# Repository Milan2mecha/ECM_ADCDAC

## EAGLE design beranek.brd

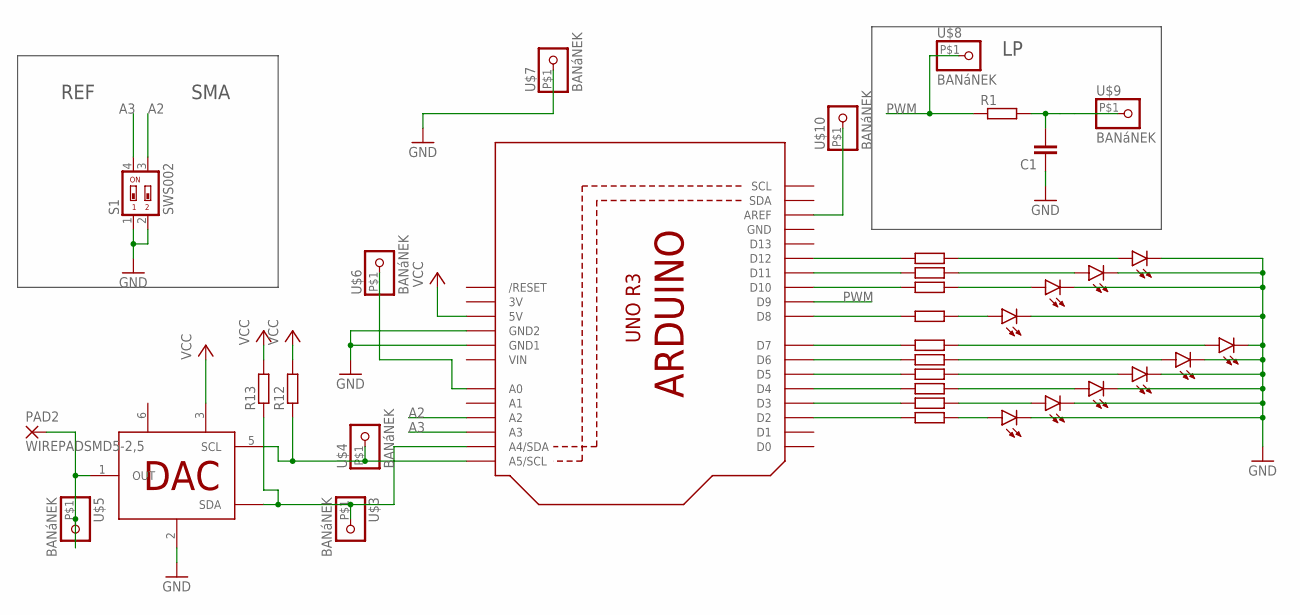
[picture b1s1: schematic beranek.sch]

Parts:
C1: C-EUC0805; C0805
LD2, LD3, LD4, LD5, LD6, LD7, LD8, LD9, LD10, LD11: PL006-WCR12; SOT23
PAD2: WIREPADSMD5-2,5; 5-2,5
Q1: ARDUINOR3-NOIOREF-NOTEXT; ARDUINOR3-NOTEXT-NOIOREF
R1, R2, R3, R4, R5, R6, R7, R8, R9, R10, R11: R-EU_R1206; R1206
R12, R13: R-EU_R0805; R0805
S1: SWS002; SMS-002
U$1: MCP4726; TSOT23-6
U$3, U$4, U$5, U$6, U$7, U$8, U$9, U$10: BANáNEK; BANANEK

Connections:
3V: Q1.3V
A2: Q1.A2, S1.3
A3: Q1.A3, S1.4
GND: C1.1, LD2.3 (C), LD3.3 (C), LD4.3 (C), LD5.3 (C), LD6.3 (C), LD7.3 (C), LD8.3 (C), LD9.3 (C), LD10.3 (C), LD11.3 (C), Q1.GND, Q1.GND1, Q1.GND2, S1.1, S1.2, U$1.2 (VSS), U$7.P$1
unnamed: PAD2.1, U$1.1 (OUT), U$5.P$1
unnamed: Q1.A4 (A4/SDA), R13.1, U$1.4 (SDA), U$3.P$1
unnamed: Q1.A0, U$6.P$1
unnamed: C1.2, R1.2, U$9.P$1
unnamed: Q1.D2, R2.2
unnamed: Q1.D3, R3.2
unnamed: Q1.D4, R4.2
unnamed: Q1.D5, R5.2
unnamed: Q1.D6, R6.2
unnamed: Q1.D7, R7.2
unnamed: Q1.D8, R8.2
unnamed: LD2.1 (A), R2.1
unnamed: LD3.1 (A), R3.1
unnamed: LD4.1 (A), R4.1
unnamed: LD7.1 (A), R7.1
unnamed: LD6.1 (A), R6.1
unnamed: LD5.1 (A), R5.1
unnamed: LD8.1 (A), R8.1
unnamed: Q1.D10, R9.2
unnamed: LD9.1 (A), R9.1
unnamed: Q1.D11, R10.2
unnamed: LD10.1 (A), R10.1
unnamed: Q1.D12, R11.2
unnamed: LD11.1 (A), R11.1
unnamed: Q1.AREF, U$10.P$1
PWM: Q1.D9, R1.1, U$8.P$1
SCL: Q1.A5 (A5/SCL), R12.1, U$1.5 (SCL), U$4.P$1
VCC: Q1.5V, R12.2, R13.2, U$1.3 (VDD)
VIN: Q1.VIN

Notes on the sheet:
REF
SMA

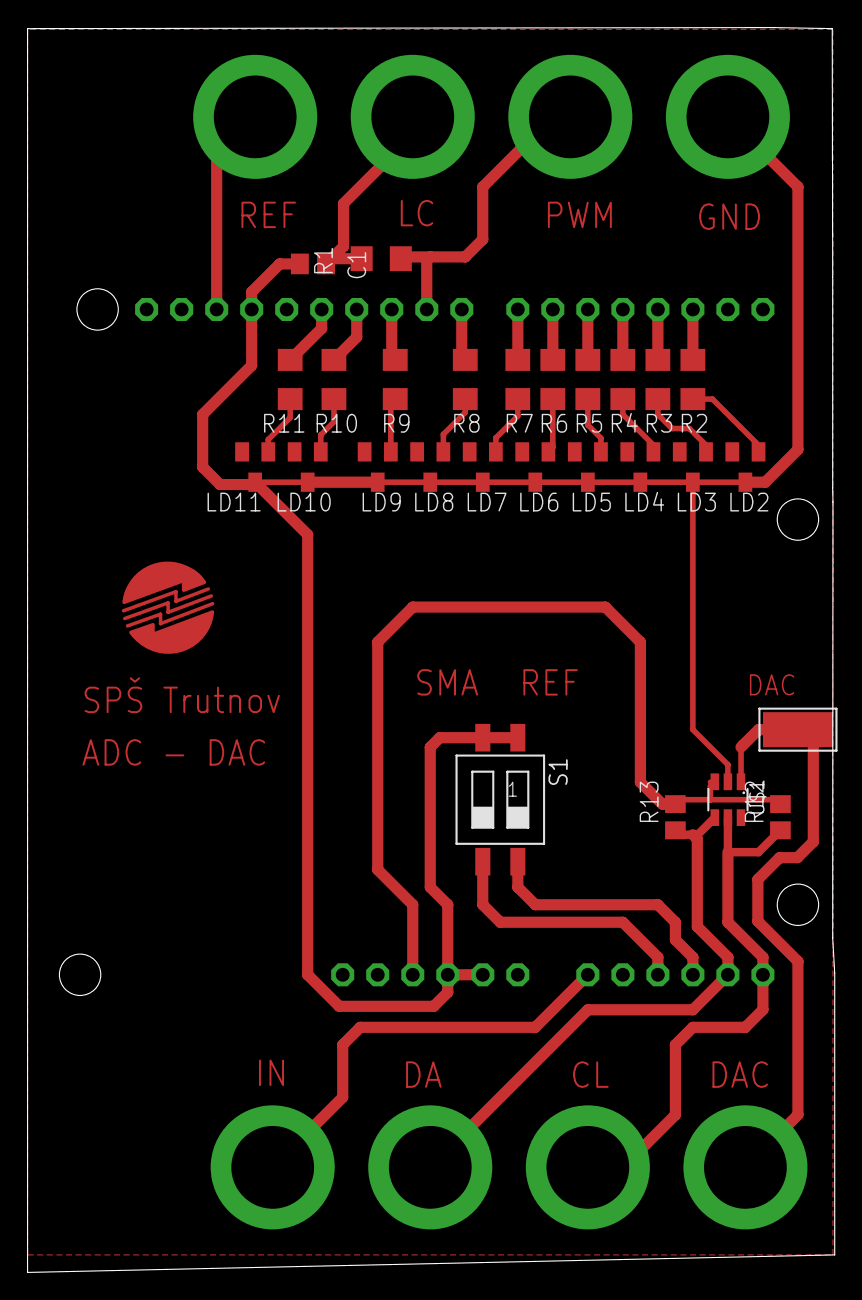
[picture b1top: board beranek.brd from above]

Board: 2 copper layers, 58.5 x 90.3 mm, 37 parts (0 on the bottom side), 31 nets.

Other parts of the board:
U$2: LOGO_SPS_TRUTNOV

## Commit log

2022-06-02 počáteční commit
2022-06-02 oprava off 1 chyby
